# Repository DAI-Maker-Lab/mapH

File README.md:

<h1>mapH</h1>
mapH is a handheld georeferenced soil pH meter originally built as a demo for the 2018 Cracking the Nut conference. It was meant to illustrate potential applications of novel approaches to small-scale hardware development and production to climate smart agriculture in developing country contexts. It is based on the [DF Robot Analog Spear Tip pH sensor](https://www.dfrobot.com/product-1668.html), Arduino Pro Micro, and the Adafruit FONA 808.

It was just a proof-of-concept demo, so it's pretty rough. It uploads a CSV of the pH reading and the GPS coordinate to Pastebin where it can then be brought into a more useful analysis tool, like Mapbox or OpenGIS.

<h3>Usage</h3>
Turn the switch to the on position. When the green LED is lit and the red is off, the unit has a valid GPS fix and the user can take a sample. Place the soil probe into the soil to be sampled and press the button. The LEDs will flash while a series of 100 readings are very quickly taken and averaged. The red LED will light and the green will turn off, indicating that the reading is being transmitted to the server. When the green LED is lit, the unit is ready to take another sample.

<h3>Research Questions</h3>
mapH was developed as a demonstration of the potential of custom hardware to serve the needs of developing country users in the area of climate smart agriculture. It was developed on the hypothesis that awareness of the relative pH differences of farmers' fields could enable more efficient and effective application of fertilizers and other inputs. Similar tools, scaled for developed country farmers, are available commercially on the same principle (and a review of the literature on the effectiveness of these in practice would be interesting in itself).

Unanswered questions regarding the demo hardware might include:

* Does it in fact accurately read soil pH levels?
* Is this in fact useful when compared with other tools available to farmers, specifically in developing country contexts (i.e., smallholder farmers with limited capital infrastructure)?
* Are there modifications that would make the device more useful?
* What is the best protocol for using the device (in terms of cleaning and caring for the probe, calibration, choosing a sample site, depth of sample, etc.)?
* How might a farmer use the data from the tool to make changes to their farming practices?

<h3>Errata</h3>
The v0.1 design erroneously routed Pin 3 from the pH sensor to D12 on the Arduino; it should have gone to A0 as in the v0.2.

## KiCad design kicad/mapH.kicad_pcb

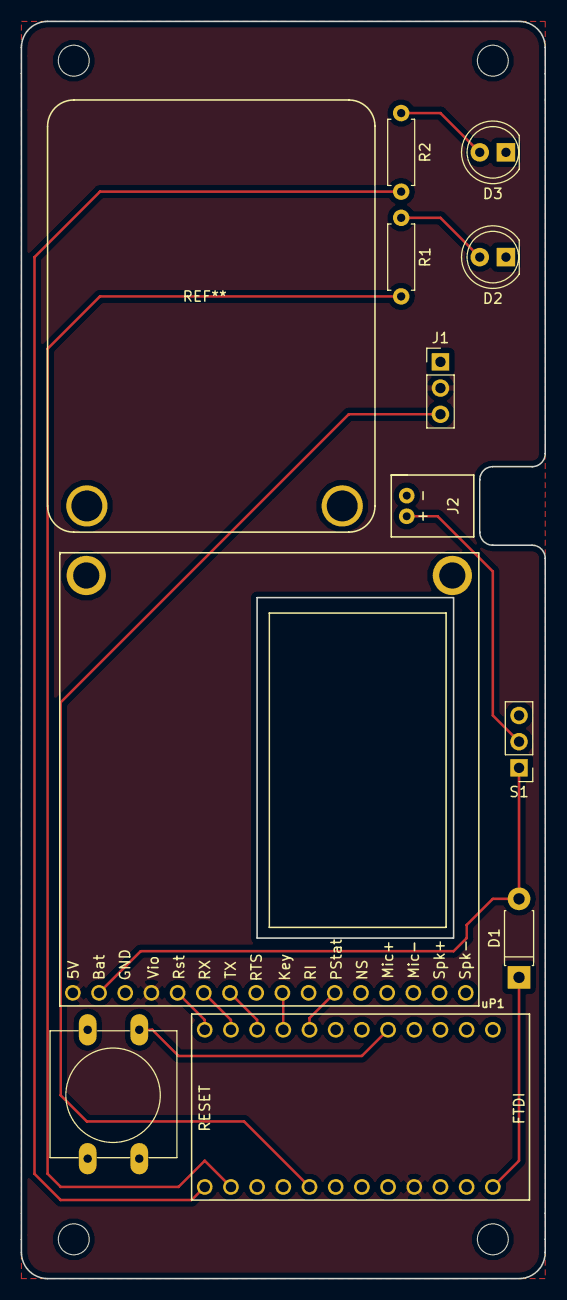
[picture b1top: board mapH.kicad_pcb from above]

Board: 2 copper layers, 50.8 x 121.9 mm, 12 parts (1 on the bottom side), 16 nets.

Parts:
D1: D; D_DO-41_SOD81_P7.62mm_Horizontal
D2: RED; LED_D5.0mm_FlatTop
D3: GREEN; LED_D5.0mm_FlatTop
J1: DFRobot; Socket_Strip_Straight_1x03_Pitch2.54mm
J2: JST; JST-PH-2
R1, R2: R; R_Axial_DIN0207_L6.3mm_D2.5mm_P7.62mm_Horizontal
S1: Power; Socket_Strip_Straight_1x03_Pitch2.54mm
S2: DTS-3; SW_PUSH-12mm
U1: FONA_808
makerlabqr: makerlabqr
uP1: ARDUPROMINI-6; Arduino_Pro_Mini-6

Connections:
BAT+: D1.2, S1.1, U1.2
GND: D2.1, D3.1, J1.1, J2.2, S2.2, U1.3, uP1.10, uP1.20
INT0: S2.1, uP1.11
unnamed: D1.1, uP1.19
unnamed: D2.2, R1.1
unnamed: D3.2, R2.1
unnamed: J1.3, uP1.26
unnamed: J2.1, S1.2
unnamed: R1.2, uP1.29
unnamed: R2.2, uP1.30
unnamed: U1.5, uP1.18
unnamed: U1.6, uP1.17
unnamed: U1.7, uP1.16
unnamed: U1.9, uP1.15
unnamed: U1.11, uP1.14
VCC: J1.2, U1.1, U1.4, uP1.22
